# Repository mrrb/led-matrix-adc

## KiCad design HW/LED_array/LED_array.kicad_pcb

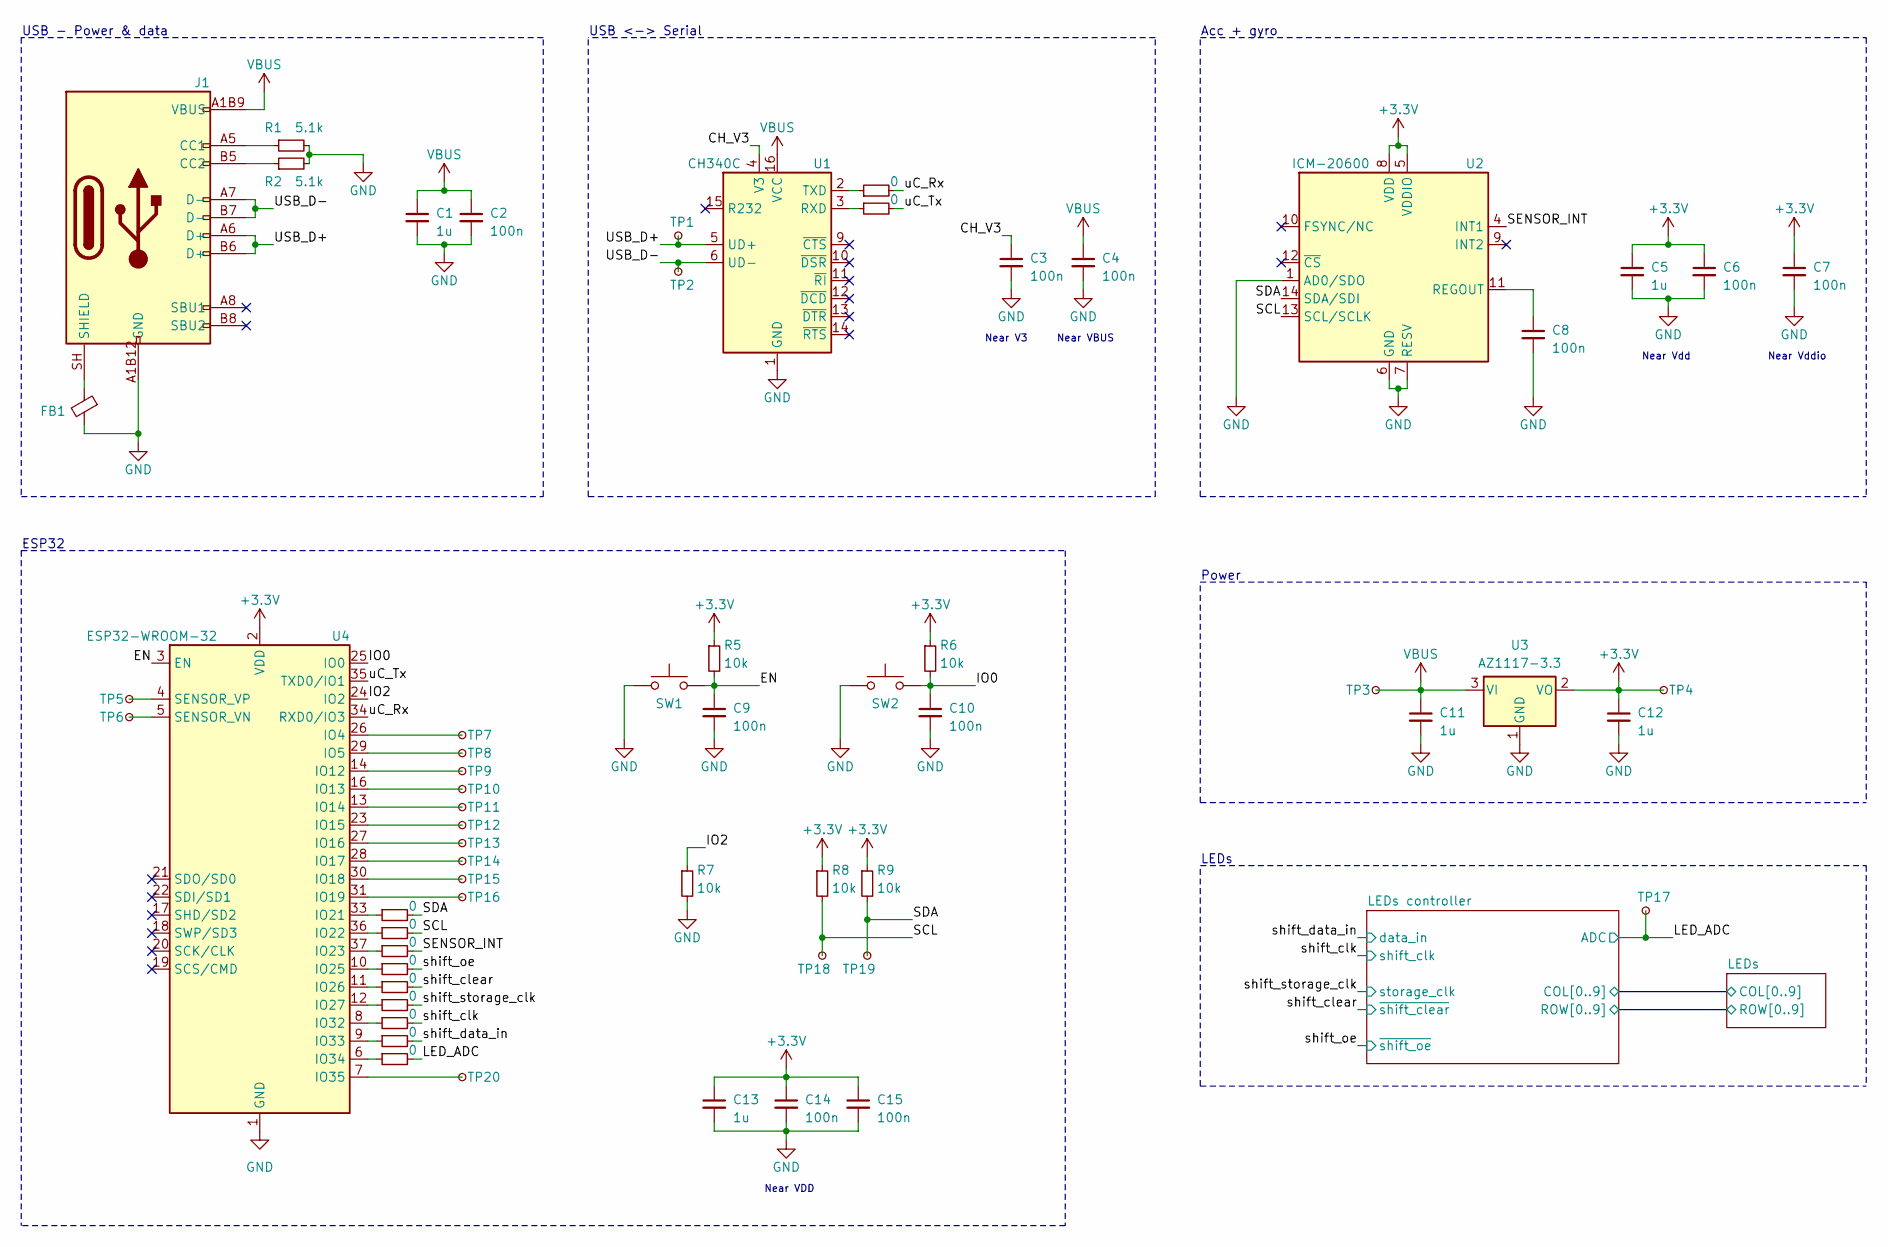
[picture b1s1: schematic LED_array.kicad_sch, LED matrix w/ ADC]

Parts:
C1, C5, C11, C12, C13: 1u; C_0603_1608Metric
C2, C3, C4, C6, C7, C8, C9, C10, C14, C15: 100n; C_0603_1608Metric
FB1: Ferrite_Bead_Small; L_0603_1608Metric
J1: TYPE-C-31-M-12; LCSC part C165948
R1, R2: 5.1k; R_0603_1608Metric
R3, R4, R10, R11, R12, R13, R14, R15, R16, R17, R18: 0; R_0603_1608Metric
R5, R6, R7, R8, R9: 10k; R_0603_1608Metric
SW1, SW2: SW_Push; TS342A2P-WZ
TP1, TP2, TP3, TP4, TP5, TP6, TP7, TP8, TP9, TP10, TP11, TP12, TP13, TP14, TP15, TP16, TP17, TP18, TP19, TP20: TestPoint_Small; TestPoint_Pad_D1.5mm
U1: CH340C; SOIC-16_3.9x9.9mm_P1.27mm
U2: ICM-20600; LGA-14_3x2.5mm_P0.5mm_LayoutBorder3x4y; LCSC C124140
U3: AZ1117-3.3; SOT-223-3_TabPin2
U4: ESP32-WROOM-32

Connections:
+3V3: C5.1, C6.1, C7.1, C12.1, C13.1, C14.1, C15.1, R5.1, R6.1, R8.1, R9.1, TP4.1, U2.5 (VDDIO), U2.8 (VDD), U3.2 (VO), U4.2 (VDD); also elsewhere on the board
/CH_V3: C3.1, U1.4 (V3)
/EN: C9.1, R5.2, SW1.2, U4.3 (EN)
/IO0: C10.1, R6.2, SW2.2, U4.25 (IO0)
/IO2: R7.1, U4.24 (IO2)
/LED_ADC: R18.2, TP17.1; also elsewhere on the board
/SCL: R8.2, R11.2, TP18.1, U2.13 (SCL/SCLK)
/SDA: R9.2, R10.2, TP19.1, U2.14 (SDA/SDI)
/SENSOR_INT: R12.2, U2.4 (INT1)
/USB_D+: J1.A6 (D+), J1.B6 (D+), TP1.1, U1.5 (UD+)
/USB_D-: J1.A7 (D-), J1.B7 (D-), TP2.1, U1.6 (UD-)
/shift_clear: R14.2; also elsewhere on the board
/shift_clk: R16.2; also elsewhere on the board
/shift_data_in: R17.2; also elsewhere on the board
/shift_oe: R13.2; also elsewhere on the board
/shift_storage_clk: R15.2; also elsewhere on the board
/uC_Rx: R3.2, U4.34 (RXD0/IO3)
/uC_Tx: R4.2, U4.35 (TXD0/IO1)
GND: C1.2, C2.2, C3.2, C4.2, C5.2, C6.2, C7.2, C8.2, C9.2, C10.2, C11.2, C12.2, C13.2, C14.2, C15.2, FB1.2, J1.A1B12 (GND), J1.B1A12 (GND), R1.2, R2.2, R7.2, SW1.1, SW2.1, U1.1 (GND), U2.1 (AD0/SDO), U2.6 (GND), U2.7 (RESV), U3.1 (GND), U4.1 (GND), U4.15 (GND), U4.38 (GND), U4.39 (GND); also elsewhere on the board
unnamed: C8.1, U2.11 (REGOUT)
unnamed: FB1.1, J1.SH (SHIELD)
unnamed: J1.A5 (CC1), R1.1
unnamed: J1.B5 (CC2), R2.1
unnamed: R3.1, U1.2 (TXD)
unnamed: R4.1, U1.3 (RXD)
unnamed: R10.1, U4.33 (IO21)
unnamed: R11.1, U4.36 (IO22)
unnamed: R12.1, U4.37 (IO23)
unnamed: R13.1, U4.10 (IO25)
unnamed: R14.1, U4.11 (IO26)
unnamed: R15.1, U4.12 (IO27)
unnamed: R16.1, U4.8 (IO32)
unnamed: R17.1, U4.9 (IO33)
unnamed: R18.1, U4.6 (IO34)
unnamed: TP5.1, U4.4 (SENSOR_VP)
unnamed: TP6.1, U4.5 (SENSOR_VN)
unnamed: TP7.1, U4.26 (IO4)
unnamed: TP8.1, U4.29 (IO5)
unnamed: TP9.1, U4.14 (IO12)
unnamed: TP10.1, U4.16 (IO13)
unnamed: TP11.1, U4.13 (IO14)
unnamed: TP12.1, U4.23 (IO15)
unnamed: TP13.1, U4.27 (IO16)
unnamed: TP14.1, U4.28 (IO17)
unnamed: TP15.1, U4.30 (IO18)
unnamed: TP16.1, U4.31 (IO19)
unnamed: TP20.1, U4.7 (IO35)
VBUS: C1.1, C2.1, C4.1, C11.1, J1.A1B9 (VBUS), J1.B1A9 (VBUS), TP3.1, U1.16 (VCC), U3.3 (VI)

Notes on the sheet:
USB - Power & data
ESP32
USB <-> Serial
Near VDD
Near V3
Near VBUS
Acc + gyro
Power
LEDs
Near Vdd
Near Vddio

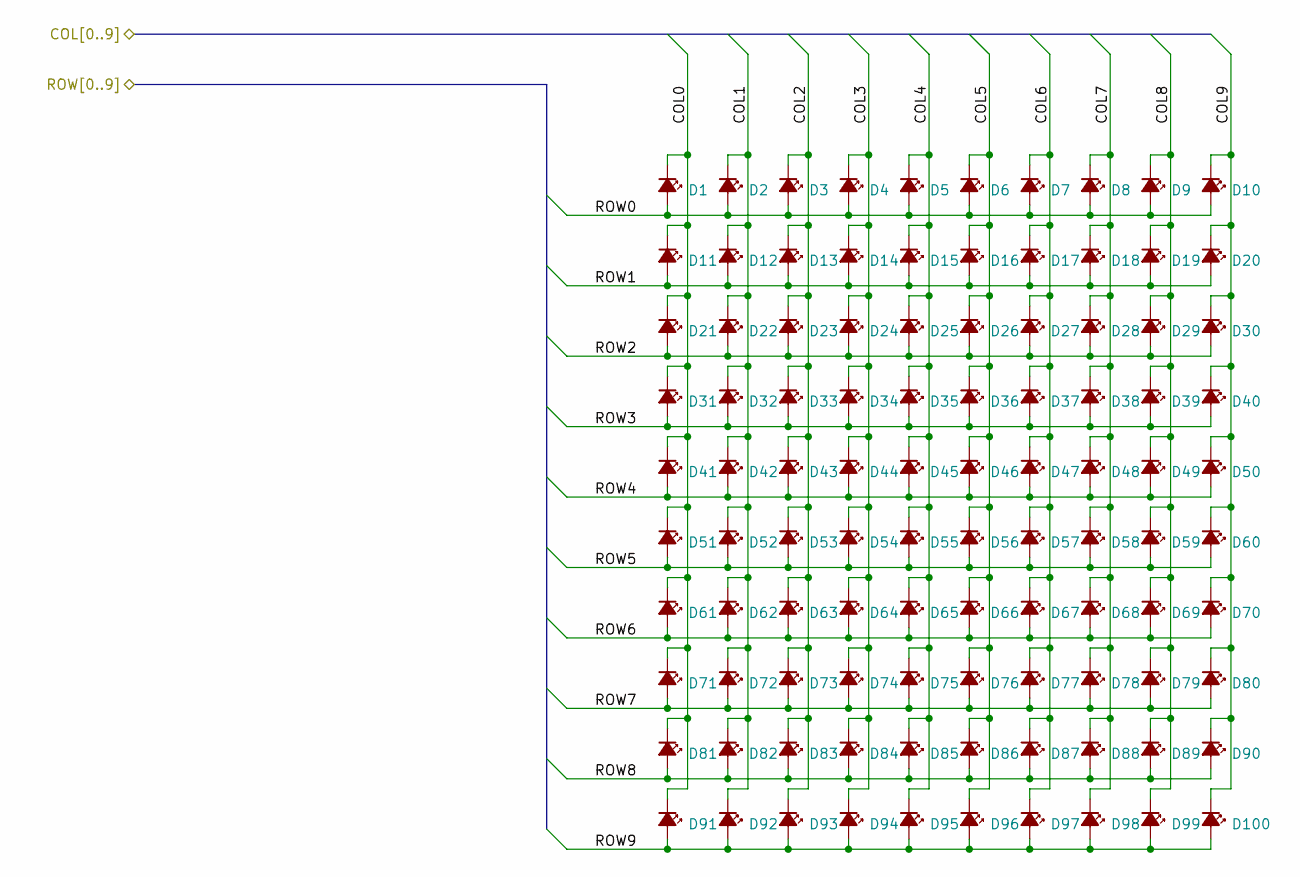
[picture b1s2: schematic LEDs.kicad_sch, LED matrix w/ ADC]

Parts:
D1, D2, D3, D4, D5, D6, D7, D8, D9, D10, D11, D12, D13, D14, D15, D16, D17, D18, D19, D20, D21, D22, D23, D24, D25, D26, D27, D28, D29, D30, D31, D32, D33, D34, D35, D36, D37, D38, D39, D40, D41, D42, D43, D44, D45, D46, D47, D48, D49, D50, D51, D52, D53, D54, D55, D56, D57, D58, D59, D60, D61, D62, D63, D64, D65, D66, D67, D68, D69, D70, D71, D72, D73, D74, D75, D76, D77, D78, D79, D80, D81, D82, D83, D84, D85, D86, D87, D88, D89, D90, D91, D92, D93, D94, D95, D96, D97, D98, D99, D100: LED_Small_ALT; LED_0805_2012Metric

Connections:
/LEDs controller/COL0: D1.1 (K), D11.1 (K), D21.1 (K), D31.1 (K), D41.1 (K), D51.1 (K), D61.1 (K), D71.1 (K), D81.1 (K), D91.1 (K); also elsewhere on the board
/LEDs controller/COL1: D2.1 (K), D12.1 (K), D22.1 (K), D32.1 (K), D42.1 (K), D52.1 (K), D62.1 (K), D72.1 (K), D82.1 (K), D92.1 (K); also elsewhere on the board
/LEDs controller/COL2: D3.1 (K), D13.1 (K), D23.1 (K), D33.1 (K), D43.1 (K), D53.1 (K), D63.1 (K), D73.1 (K), D83.1 (K), D93.1 (K); also elsewhere on the board
/LEDs controller/COL3: D4.1 (K), D14.1 (K), D24.1 (K), D34.1 (K), D44.1 (K), D54.1 (K), D64.1 (K), D74.1 (K), D84.1 (K), D94.1 (K); also elsewhere on the board
/LEDs controller/COL4: D5.1 (K), D15.1 (K), D25.1 (K), D35.1 (K), D45.1 (K), D55.1 (K), D65.1 (K), D75.1 (K), D85.1 (K), D95.1 (K); also elsewhere on the board
/LEDs controller/COL5: D6.1 (K), D16.1 (K), D26.1 (K), D36.1 (K), D46.1 (K), D56.1 (K), D66.1 (K), D76.1 (K), D86.1 (K), D96.1 (K); also elsewhere on the board
/LEDs controller/COL6: D7.1 (K), D17.1 (K), D27.1 (K), D37.1 (K), D47.1 (K), D57.1 (K), D67.1 (K), D77.1 (K), D87.1 (K), D97.1 (K); also elsewhere on the board
/LEDs controller/COL7: D8.1 (K), D18.1 (K), D28.1 (K), D38.1 (K), D48.1 (K), D58.1 (K), D68.1 (K), D78.1 (K), D88.1 (K), D98.1 (K); also elsewhere on the board
/LEDs controller/COL8: D9.1 (K), D19.1 (K), D29.1 (K), D39.1 (K), D49.1 (K), D59.1 (K), D69.1 (K), D79.1 (K), D89.1 (K), D99.1 (K); also elsewhere on the board
/LEDs controller/COL9: D10.1 (K), D20.1 (K), D30.1 (K), D40.1 (K), D50.1 (K), D60.1 (K), D70.1 (K), D80.1 (K), D90.1 (K), D100.1 (K); also elsewhere on the board
/LEDs controller/ROW0: D1.2 (A), D2.2 (A), D3.2 (A), D4.2 (A), D5.2 (A), D6.2 (A), D7.2 (A), D8.2 (A), D9.2 (A), D10.2 (A); also elsewhere on the board
/LEDs controller/ROW1: D11.2 (A), D12.2 (A), D13.2 (A), D14.2 (A), D15.2 (A), D16.2 (A), D17.2 (A), D18.2 (A), D19.2 (A), D20.2 (A); also elsewhere on the board
/LEDs controller/ROW2: D21.2 (A), D22.2 (A), D23.2 (A), D24.2 (A), D25.2 (A), D26.2 (A), D27.2 (A), D28.2 (A), D29.2 (A), D30.2 (A); also elsewhere on the board
/LEDs controller/ROW3: D31.2 (A), D32.2 (A), D33.2 (A), D34.2 (A), D35.2 (A), D36.2 (A), D37.2 (A), D38.2 (A), D39.2 (A), D40.2 (A); also elsewhere on the board
/LEDs controller/ROW4: D41.2 (A), D42.2 (A), D43.2 (A), D44.2 (A), D45.2 (A), D46.2 (A), D47.2 (A), D48.2 (A), D49.2 (A), D50.2 (A); also elsewhere on the board
/LEDs controller/ROW5: D51.2 (A), D52.2 (A), D53.2 (A), D54.2 (A), D55.2 (A), D56.2 (A), D57.2 (A), D58.2 (A), D59.2 (A), D60.2 (A); also elsewhere on the board
/LEDs controller/ROW6: D61.2 (A), D62.2 (A), D63.2 (A), D64.2 (A), D65.2 (A), D66.2 (A), D67.2 (A), D68.2 (A), D69.2 (A), D70.2 (A); also elsewhere on the board
/LEDs controller/ROW7: D71.2 (A), D72.2 (A), D73.2 (A), D74.2 (A), D75.2 (A), D76.2 (A), D77.2 (A), D78.2 (A), D79.2 (A), D80.2 (A); also elsewhere on the board
/LEDs controller/ROW8: D81.2 (A), D82.2 (A), D83.2 (A), D84.2 (A), D85.2 (A), D86.2 (A), D87.2 (A), D88.2 (A), D89.2 (A), D90.2 (A); also elsewhere on the board
/LEDs controller/ROW9: D91.2 (A), D92.2 (A), D93.2 (A), D94.2 (A), D95.2 (A), D96.2 (A), D97.2 (A), D98.2 (A), D99.2 (A), D100.2 (A); also elsewhere on the board

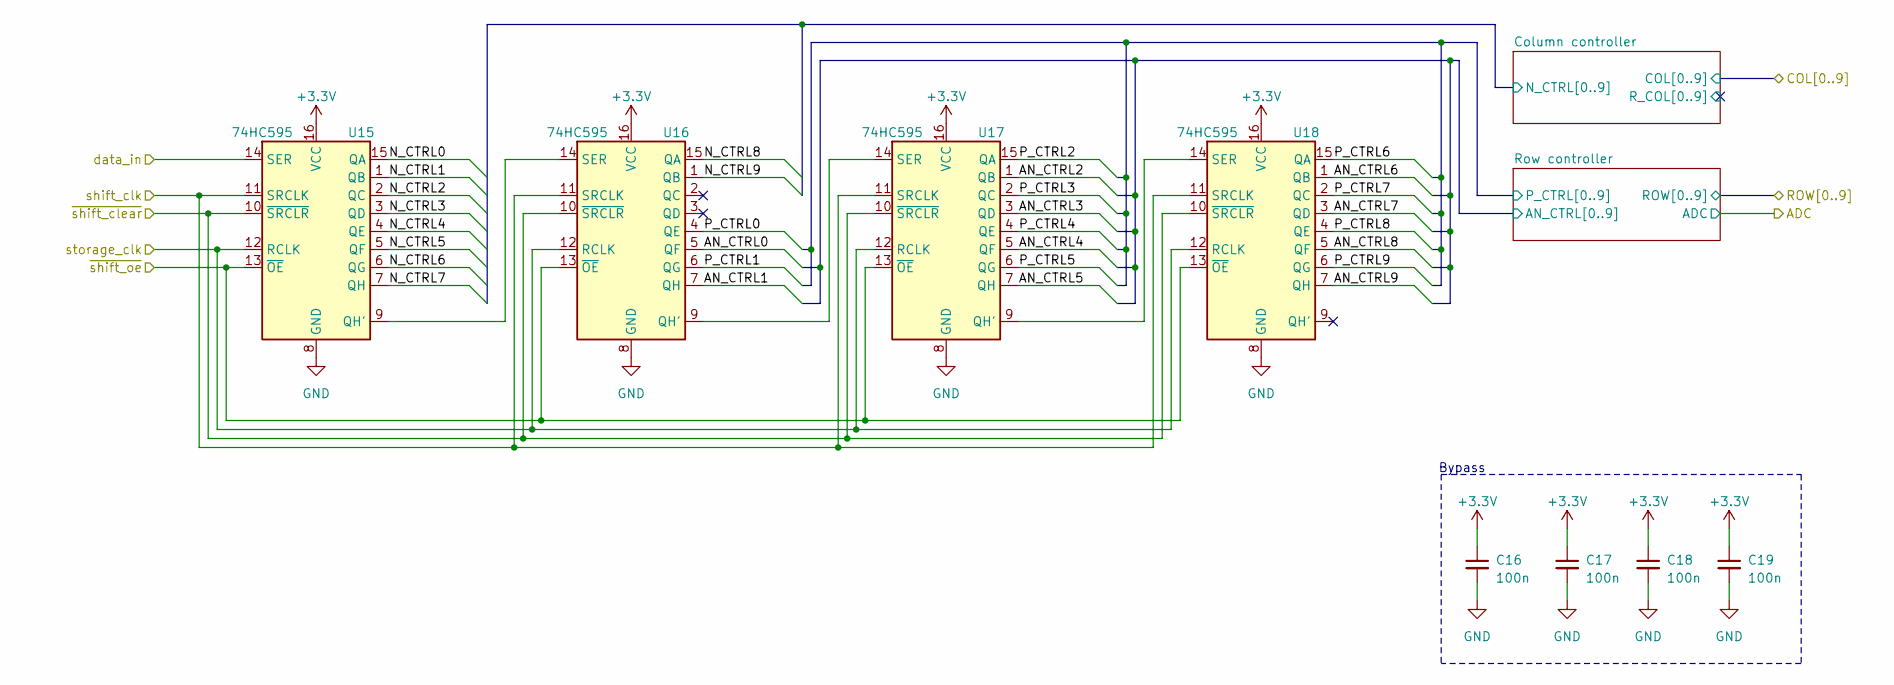
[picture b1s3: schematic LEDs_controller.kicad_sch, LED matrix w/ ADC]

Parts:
C16, C17, C18, C19: 100n; C_0603_1608Metric
U15, U16, U17, U18: 74HC595; SOP-16_3.9x9.9mm_P1.27mm; LCSC C2798023

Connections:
+3V3: C16.1, C17.1, C18.1, C19.1, U15.16 (VCC), U16.16 (VCC), U17.16 (VCC), U18.16 (VCC); also elsewhere on the board
/LEDs controller/Column controller/N_CTRL0: U15.15 (QA); also elsewhere on the board
/LEDs controller/Column controller/N_CTRL1: U15.1 (QB); also elsewhere on the board
/LEDs controller/Column controller/N_CTRL2: U15.2 (QC); also elsewhere on the board
/LEDs controller/Column controller/N_CTRL3: U15.3 (QD); also elsewhere on the board
/LEDs controller/Column controller/N_CTRL4: U15.4 (QE); also elsewhere on the board
/LEDs controller/Column controller/N_CTRL5: U15.5 (QF); also elsewhere on the board
/LEDs controller/Column controller/N_CTRL6: U15.6 (QG); also elsewhere on the board
/LEDs controller/Column controller/N_CTRL7: U15.7 (QH); also elsewhere on the board
/LEDs controller/Column controller/N_CTRL8: U16.15 (QA); also elsewhere on the board
/LEDs controller/Column controller/N_CTRL9: U16.1 (QB); also elsewhere on the board
/LEDs controller/Row controller/AN_CTRL0: U16.5 (QF); also elsewhere on the board
/LEDs controller/Row controller/AN_CTRL1: U16.7 (QH); also elsewhere on the board
/LEDs controller/Row controller/AN_CTRL2: U17.1 (QB); also elsewhere on the board
/LEDs controller/Row controller/AN_CTRL3: U17.3 (QD); also elsewhere on the board
/LEDs controller/Row controller/AN_CTRL4: U17.5 (QF); also elsewhere on the board
/LEDs controller/Row controller/AN_CTRL5: U17.7 (QH); also elsewhere on the board
/LEDs controller/Row controller/AN_CTRL6: U18.1 (QB); also elsewhere on the board
/LEDs controller/Row controller/AN_CTRL7: U18.3 (QD); also elsewhere on the board
/LEDs controller/Row controller/AN_CTRL8: U18.5 (QF); also elsewhere on the board
/LEDs controller/Row controller/AN_CTRL9: U18.7 (QH); also elsewhere on the board
/LEDs controller/Row controller/P_CTRL0: U16.4 (QE); also elsewhere on the board
/LEDs controller/Row controller/P_CTRL1: U16.6 (QG); also elsewhere on the board
/LEDs controller/Row controller/P_CTRL2: U17.15 (QA); also elsewhere on the board
/LEDs controller/Row controller/P_CTRL3: U17.2 (QC); also elsewhere on the board
/LEDs controller/Row controller/P_CTRL4: U17.4 (QE); also elsewhere on the board
/LEDs controller/Row controller/P_CTRL5: U17.6 (QG); also elsewhere on the board
/LEDs controller/Row controller/P_CTRL6: U18.15 (QA); also elsewhere on the board
/LEDs controller/Row controller/P_CTRL7: U18.2 (QC); also elsewhere on the board
/LEDs controller/Row controller/P_CTRL8: U18.4 (QE); also elsewhere on the board
/LEDs controller/Row controller/P_CTRL9: U18.6 (QG); also elsewhere on the board
/shift_clear: U15.10 (~SRCLR), U16.10 (~SRCLR), U17.10 (~SRCLR), U18.10 (~SRCLR); also elsewhere on the board
/shift_clk: U15.11 (SRCLK), U16.11 (SRCLK), U17.11 (SRCLK), U18.11 (SRCLK); also elsewhere on the board
/shift_data_in: U15.14 (SER); also elsewhere on the board
/shift_oe: U15.13 (~OE), U16.13 (~OE), U17.13 (~OE), U18.13 (~OE); also elsewhere on the board
/shift_storage_clk: U15.12 (RCLK), U16.12 (RCLK), U17.12 (RCLK), U18.12 (RCLK); also elsewhere on the board
GND: C16.2, C17.2, C18.2, C19.2, U15.8 (GND), U16.8 (GND), U17.8 (GND), U18.8 (GND); also elsewhere on the board
unnamed: U15.9 (QH'), U16.14 (SER)
unnamed: U16.9 (QH'), U17.14 (SER)
unnamed: U17.9 (QH'), U18.14 (SER)

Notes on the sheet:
Bypass

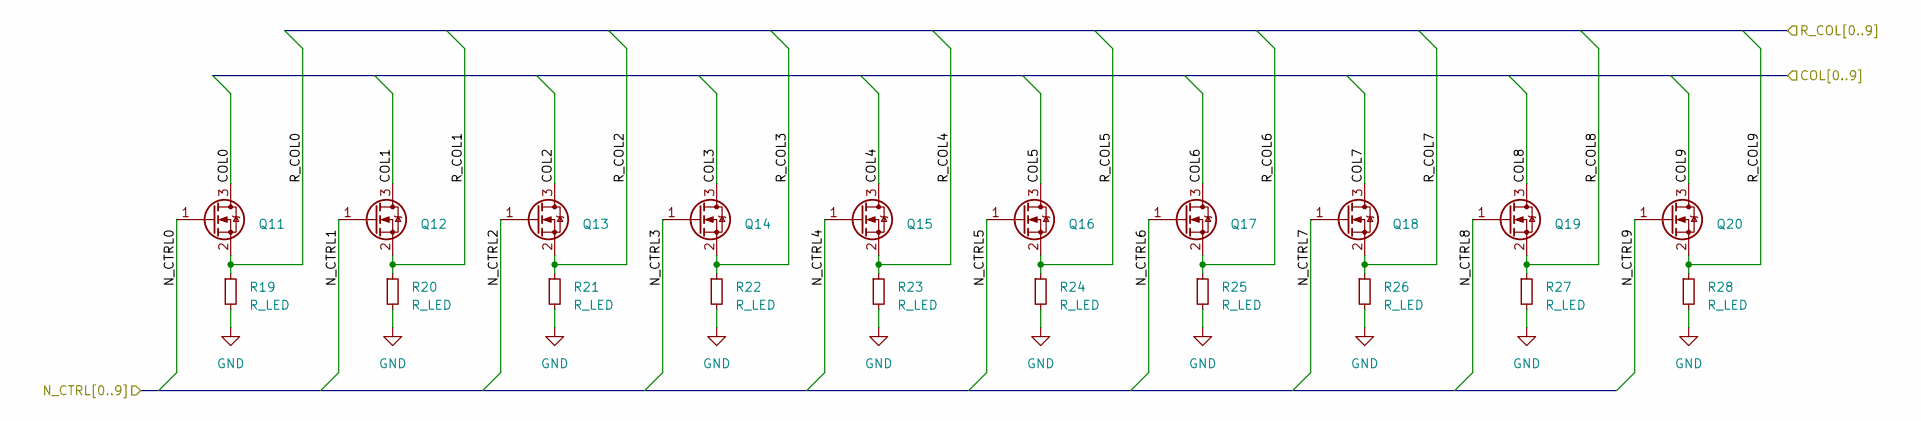
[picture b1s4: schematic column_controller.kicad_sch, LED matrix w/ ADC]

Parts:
Q11, Q12, Q13, Q14, Q15, Q16, Q17, Q18, Q19, Q20: Q_NMOS_GSD; SOT-23; LCSC C296295
R19, R20, R21, R22, R23, R24, R25, R26, R27, R28: R_LED; R_0603_1608Metric

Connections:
/LEDs controller/COL0: Q11.3 (D); also elsewhere on the board
/LEDs controller/COL1: Q12.3 (D); also elsewhere on the board
/LEDs controller/COL2: Q13.3 (D); also elsewhere on the board
/LEDs controller/COL3: Q14.3 (D); also elsewhere on the board
/LEDs controller/COL4: Q15.3 (D); also elsewhere on the board
/LEDs controller/COL5: Q16.3 (D); also elsewhere on the board
/LEDs controller/COL6: Q17.3 (D); also elsewhere on the board
/LEDs controller/COL7: Q18.3 (D); also elsewhere on the board
/LEDs controller/COL8: Q19.3 (D); also elsewhere on the board
/LEDs controller/COL9: Q20.3 (D); also elsewhere on the board
/LEDs controller/Column controller/N_CTRL0: Q11.1 (G); also elsewhere on the board
/LEDs controller/Column controller/N_CTRL1: Q12.1 (G); also elsewhere on the board
/LEDs controller/Column controller/N_CTRL2: Q13.1 (G); also elsewhere on the board
/LEDs controller/Column controller/N_CTRL3: Q14.1 (G); also elsewhere on the board
/LEDs controller/Column controller/N_CTRL4: Q15.1 (G); also elsewhere on the board
/LEDs controller/Column controller/N_CTRL5: Q16.1 (G); also elsewhere on the board
/LEDs controller/Column controller/N_CTRL6: Q17.1 (G); also elsewhere on the board
/LEDs controller/Column controller/N_CTRL7: Q18.1 (G); also elsewhere on the board
/LEDs controller/Column controller/N_CTRL8: Q19.1 (G); also elsewhere on the board
/LEDs controller/Column controller/N_CTRL9: Q20.1 (G); also elsewhere on the board
/LEDs controller/Column controller/R_COL0: Q11.2 (S), R19.1
/LEDs controller/Column controller/R_COL1: Q12.2 (S), R20.1
/LEDs controller/Column controller/R_COL2: Q13.2 (S), R21.1
/LEDs controller/Column controller/R_COL3: Q14.2 (S), R22.1
/LEDs controller/Column controller/R_COL4: Q15.2 (S), R23.1
/LEDs controller/Column controller/R_COL5: Q16.2 (S), R24.1
/LEDs controller/Column controller/R_COL6: Q17.2 (S), R25.1
/LEDs controller/Column controller/R_COL7: Q18.2 (S), R26.1
/LEDs controller/Column controller/R_COL8: Q19.2 (S), R27.1
/LEDs controller/Column controller/R_COL9: Q20.2 (S), R28.1
GND: R19.2, R20.2, R21.2, R22.2, R23.2, R24.2, R25.2, R26.2, R27.2, R28.2; also elsewhere on the board

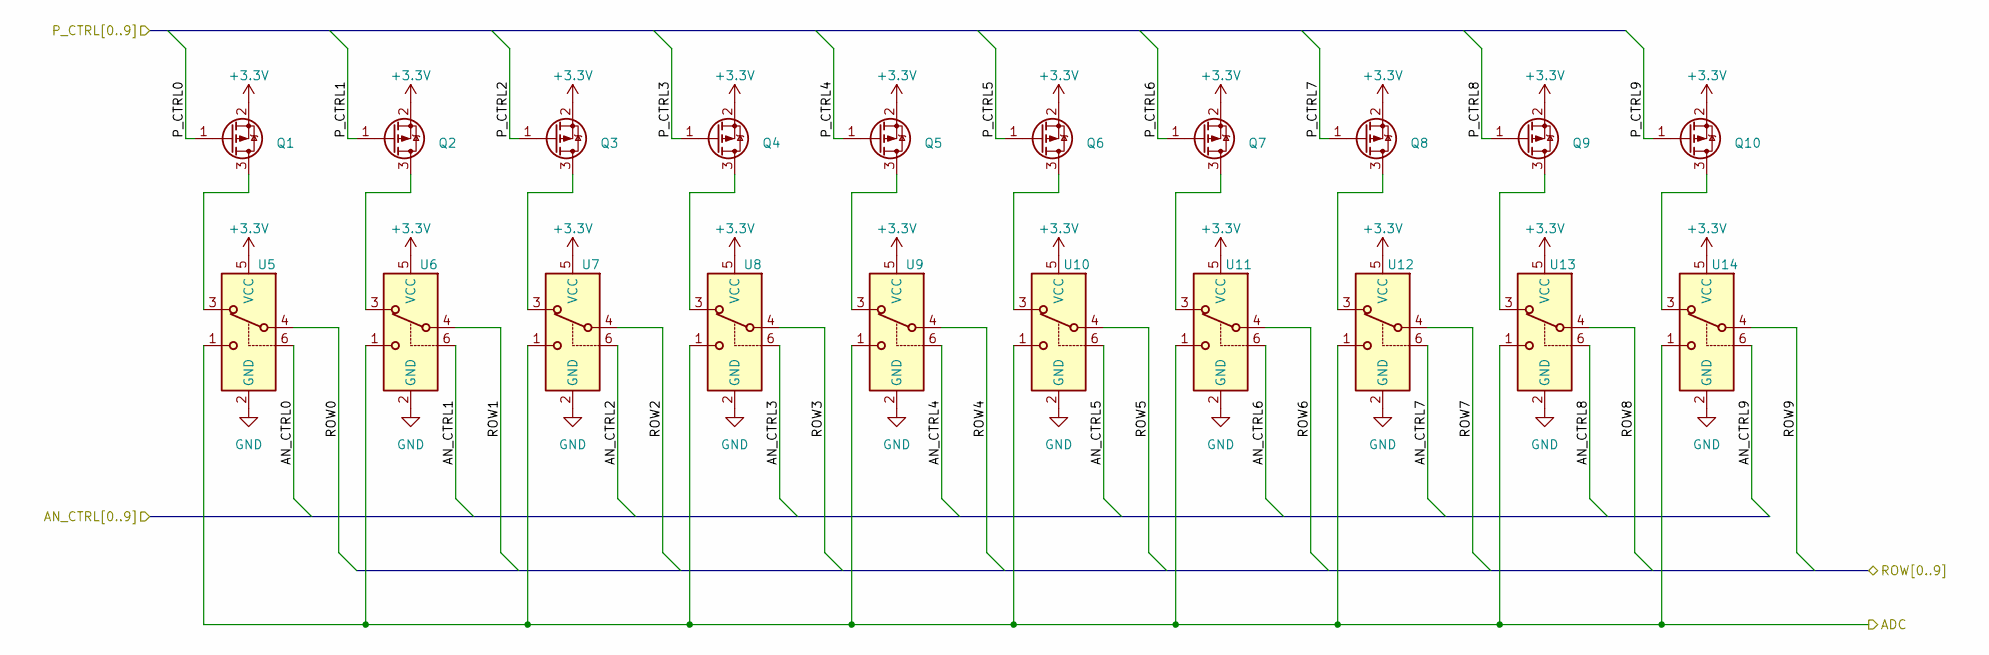
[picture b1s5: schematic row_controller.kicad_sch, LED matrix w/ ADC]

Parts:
Q1, Q2, Q3, Q4, Q5, Q6, Q7, Q8, Q9, Q10: Q_PMOS_GSD; SOT-23; LCSC C296296
U5, U6, U7, U8, U9, U10, U11, U12, U13, U14: BL1551; SC-70-8; LCSC C82528

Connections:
+3V3: Q1.2 (S), Q2.2 (S), Q3.2 (S), Q4.2 (S), Q5.2 (S), Q6.2 (S), Q7.2 (S), Q8.2 (S), Q9.2 (S), Q10.2 (S), U5.5 (VCC), U6.5 (VCC), U7.5 (VCC), U8.5 (VCC), U9.5 (VCC), U10.5 (VCC), U11.5 (VCC), U12.5 (VCC), U13.5 (VCC), U14.5 (VCC); also elsewhere on the board
/LED_ADC: U5.1, U6.1, U7.1, U8.1, U9.1, U10.1, U11.1, U12.1, U13.1, U14.1; also elsewhere on the board
/LEDs controller/ROW0: U5.4; also elsewhere on the board
/LEDs controller/ROW1: U6.4; also elsewhere on the board
/LEDs controller/ROW2: U7.4; also elsewhere on the board
/LEDs controller/ROW3: U8.4; also elsewhere on the board
/LEDs controller/ROW4: U9.4; also elsewhere on the board
/LEDs controller/ROW5: U10.4; also elsewhere on the board
/LEDs controller/ROW6: U11.4; also elsewhere on the board
/LEDs controller/ROW7: U12.4; also elsewhere on the board
/LEDs controller/ROW8: U13.4; also elsewhere on the board
/LEDs controller/ROW9: U14.4; also elsewhere on the board
/LEDs controller/Row controller/AN_CTRL0: U5.6; also elsewhere on the board
/LEDs controller/Row controller/AN_CTRL1: U6.6; also elsewhere on the board
/LEDs controller/Row controller/AN_CTRL2: U7.6; also elsewhere on the board
/LEDs controller/Row controller/AN_CTRL3: U8.6; also elsewhere on the board
/LEDs controller/Row controller/AN_CTRL4: U9.6; also elsewhere on the board
/LEDs controller/Row controller/AN_CTRL5: U10.6; also elsewhere on the board
/LEDs controller/Row controller/AN_CTRL6: U11.6; also elsewhere on the board
/LEDs controller/Row controller/AN_CTRL7: U12.6; also elsewhere on the board
/LEDs controller/Row controller/AN_CTRL8: U13.6; also elsewhere on the board
/LEDs controller/Row controller/AN_CTRL9: U14.6; also elsewhere on the board
/LEDs controller/Row controller/P_CTRL0: Q1.1 (G); also elsewhere on the board
/LEDs controller/Row controller/P_CTRL1: Q2.1 (G); also elsewhere on the board
/LEDs controller/Row controller/P_CTRL2: Q3.1 (G); also elsewhere on the board
/LEDs controller/Row controller/P_CTRL3: Q4.1 (G); also elsewhere on the board
/LEDs controller/Row controller/P_CTRL4: Q5.1 (G); also elsewhere on the board
/LEDs controller/Row controller/P_CTRL5: Q6.1 (G); also elsewhere on the board
/LEDs controller/Row controller/P_CTRL6: Q7.1 (G); also elsewhere on the board
/LEDs controller/Row controller/P_CTRL7: Q8.1 (G); also elsewhere on the board
/LEDs controller/Row controller/P_CTRL8: Q9.1 (G); also elsewhere on the board
/LEDs controller/Row controller/P_CTRL9: Q10.1 (G); also elsewhere on the board
GND: U5.2 (GND), U6.2 (GND), U7.2 (GND), U8.2 (GND), U9.2 (GND), U10.2 (GND), U11.2 (GND), U12.2 (GND), U13.2 (GND), U14.2 (GND); also elsewhere on the board
unnamed: Q1.3 (D), U5.3
unnamed: Q2.3 (D), U6.3
unnamed: Q3.3 (D), U7.3
unnamed: Q4.3 (D), U8.3
unnamed: Q5.3 (D), U9.3
unnamed: Q6.3 (D), U10.3
unnamed: Q7.3 (D), U11.3
unnamed: Q8.3 (D), U12.3
unnamed: Q9.3 (D), U13.3
unnamed: Q10.3 (D), U14.3
